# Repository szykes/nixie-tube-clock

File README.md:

# nixie-tube-clock

At first I declared my requirements for my ideal clock. Here are the requirements:
  * No touch working: there shall not be any button or something like that but the clock shall follow daylight saving time or it shall be set after a power outage.
  * Dust resistant: the dust shall not affect the visibility of clock and it shall not be on the PCB and parts.
  * Beautiful: The clock shall have maximum 2 dominant colors (PCB, parts and enclosure).
  
To implement "no touch working" I used a Wifi module to query the accureate time from my home server.
For "dust resistant" requirement I put the clock in a plastic enclosure to procect the core of clock.
"Beautiful" is implemented by selecting white PCB and mostly black parts.

## Docker

```
docker build -t time-server:v1.0 .
docker-compose up -d
```

## Hardware

### Measurements
  * Cathode voltage: 178 V
  * Cathode current: ~800 uA
  * Glim lamp current: ~250 uA
  * Total current: ~220 mA @ 12,2 V without WiFi.
  
### Known issues
  * RBG LED flahes at power-on. The gate of MOSFET of LEDs require a pull-down resistor.
  * PCB design of tube is wrong. The place drawing of tube is mirrored; therefore, digit 7 is digit 4 in real.

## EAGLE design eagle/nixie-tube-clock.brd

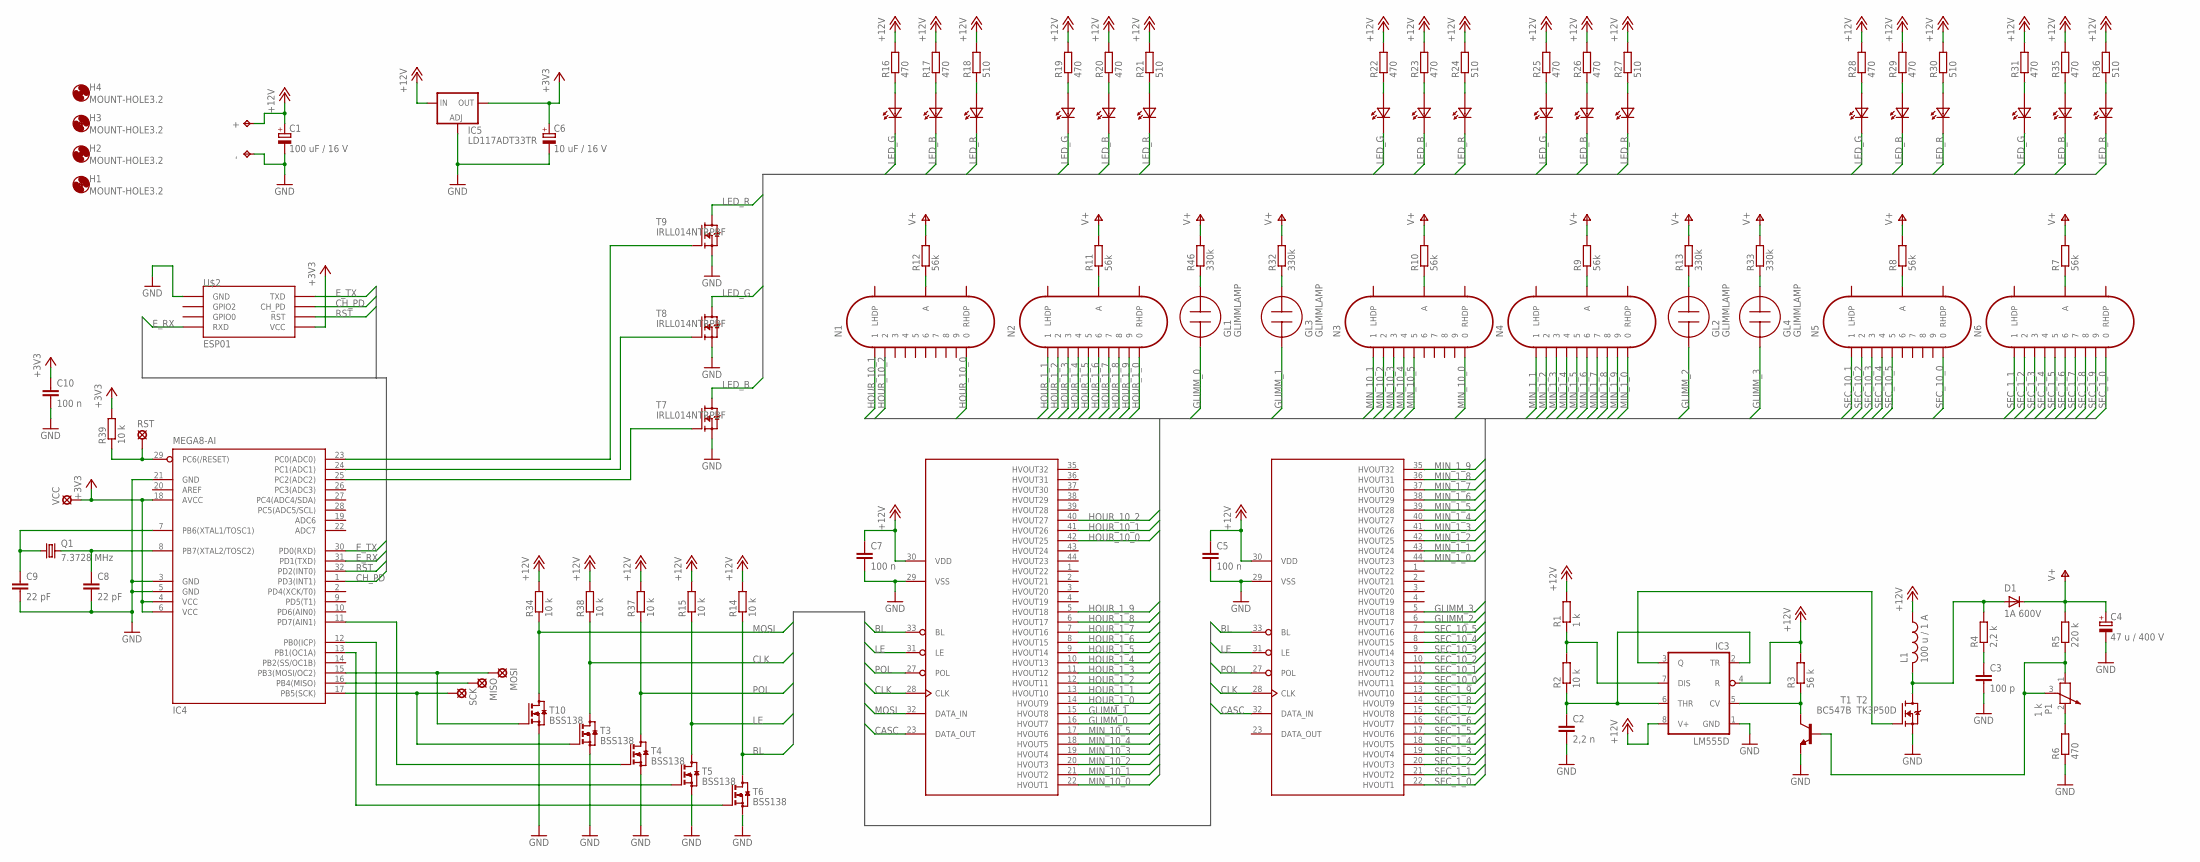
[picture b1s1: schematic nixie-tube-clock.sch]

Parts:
+: +; P1-17
-: -; P1-17
C1: 100 uF / 16 V; 153CLV-0605
C2: 2,2 n; C1206
C3: 100 p; C1206
C4: 47 u / 400 V; E7,5-16
C5, C7, C10: 100 n; C1206
C6: 10 uF / 16 V; 153CLV-0405
C8, C9: 22 pF; C1206
D1: 1A 600V; SMA-DO214AC
GL1, GL2, GL3, GL4: GLIMMLAMP
H1, H2, H3, H4: MOUNT-HOLE3.2; 3,2
IC1, IC2: HV5622QC; PQFP44
IC3: LM555D; SO08
IC4: MEGA8-AI; TQFP32-08
IC5: LD117ADT33TR; DPACK
L1: 100 u / 1 A; L_V_8.7X12_RM5.0
MISO: MISO; SE11
MOSI: MOSI; SE11
N1, N2, N3, N4, N5, N6: IN-14
P1: 1 k; PT-10
Q1: 7.3728 MHz; HC49/S
R1: 1 k; R1206
R2, R14, R15, R34, R37, R38, R39: 10 k; R1206
R3: 56 k; R1206
R4: 2,2 k; R1206
R5: 220 k; R1206
R6, R16, R17, R19, R20, R22, R23, R25, R26, R28, R29, R31, R35: 470; R1206
R7, R8, R9, R10, R11, R12: 56k; R1206
R13, R32, R33, R46: 330k; R1206
R18, R21, R24, R27, R30, R36: 510; R1206
RST: RST; SE11
SCK: SCK; SE11
T1: BC547B; SOT23-BEC
T2: TK3P50D; TO252
T3, T4, T5, T6, T10: BSS138; SOT23
T7, T8, T9: IRLL014NTRPBF; SOT223
U$1, U$3, U$4, U$5, U$6, U$7: OF-SMD5060RGB
U$2: ESP01
VCC: VCC; SE11

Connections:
+3V3: C6.+, C10.1, IC4.4 (VCC), IC4.6 (VCC), IC4.18 (AVCC), IC5.4 (OUT), R39.2, U$2.VCC, VCC.MP
+12V: +.TP, C1.+, C5.1, C7.1, IC1.30 (VDD), IC2.30 (VDD), IC3.4 (R), IC3.8 (V+), IC5.3 (IN), L1.P$1 (1), R1.2, R3.2, R14.2, R15.2, R16.2, R17.2, R18.2, R19.2, R20.2, R21.2, R22.2, R23.2, R24.2, R25.2, R26.2, R27.2, R28.2, R29.2, R30.2, R31.2, R34.2, R35.2, R36.2, R37.2, R38.2
BL: IC1.33 (BL), IC2.33 (BL), R14.1, T6.3 (D)
CASC: IC1.23 (DATA_OUT), IC2.32 (DATA_IN)
CH_PD: IC4.1 (PD3(INT1)), U$2.CH_PD
CLK: IC1.28 (CLK), IC2.28 (CLK), R38.1, T3.3 (D)
E_RX: IC4.31 (PD1(TXD)), U$2.RX (RXD)
E_TX: IC4.30 (PD0(RXD)), U$2.TX (TXD)
GLIMM_0: GL1.C, IC1.16 (HVOUT7)
GLIMM_1: GL3.C, IC1.15 (HVOUT8)
GLIMM_2: GL2.C, IC2.6 (HVOUT17)
GLIMM_3: GL4.C, IC2.5 (HVOUT18)
GND: -.TP, C1.-, C2.2, C3.2, C4.-, C5.2, C6.-, C7.2, C8.2, C9.2, C10.2, IC1.29 (VSS), IC2.29 (VSS), IC3.1 (GND), IC4.3 (GND), IC4.5 (GND), IC4.21 (GND), IC5.1 (ADJ), R6.1, T1.E, T2.2 (S), T3.2 (S), T4.2 (S), T5.2 (S), T6.2 (S), T7.3 (S), T8.3 (S), T9.3 (S), T10.2 (S), U$2.GND
HOUR_1_0: IC1.14 (HVOUT9), N2.0
HOUR_1_1: IC1.13 (HVOUT10), N2.1
HOUR_1_2: IC1.12 (HVOUT11), N2.2
HOUR_1_3: IC1.11 (HVOUT12), N2.3
HOUR_1_4: IC1.10 (HVOUT13), N2.4
HOUR_1_5: IC1.9 (HVOUT14), N2.5
HOUR_1_6: IC1.8 (HVOUT15), N2.6
HOUR_1_7: IC1.7 (HVOUT16), N2.7
HOUR_1_8: IC1.6 (HVOUT17), N2.8
HOUR_1_9: IC1.5 (HVOUT18), N2.9
HOUR_10_0: IC1.42 (HVOUT25), N1.0
HOUR_10_1: IC1.41 (HVOUT26), N1.1
HOUR_10_2: IC1.40 (HVOUT27), N1.2
LE: IC1.31 (LE), IC2.31 (LE), R15.1, T5.3 (D)
LED_B: T7.2 (D), T7.4 (D), U$1.B_CATH (CATH), U$3.B_CATH (CATH), U$4.B_CATH (CATH), U$5.B_CATH (CATH), U$6.B_CATH (CATH), U$7.B_CATH (CATH)
LED_D0: IC4.23 (PC0(ADC0)), T9.1 (G)
LED_D1: IC4.24 (PC1(ADC1)), T8.1 (G)
LED_D2: IC4.25 (PC2(ADC2)), T7.1 (G)
LED_G: T8.2 (D), T8.4 (D), U$1.G_CATH (CATH), U$3.G_CATH (CATH), U$4.G_CATH (CATH), U$5.G_CATH (CATH), U$6.G_CATH (CATH), U$7.G_CATH (CATH)
LED_R: T9.2 (D), T9.4 (D), U$1.R_CATH (CATH), U$3.R_CATH (CATH), U$4.R_CATH (CATH), U$5.R_CATH (CATH), U$6.R_CATH (CATH), U$7.R_CATH (CATH)
MIN_1_0: IC2.44 (HVOUT23), N4.0
MIN_1_1: IC2.43 (HVOUT24), N4.1
MIN_1_2: IC2.42 (HVOUT25), N4.2
MIN_1_3: IC2.41 (HVOUT26), N4.3
MIN_1_4: IC2.40 (HVOUT27), N4.4
MIN_1_5: IC2.39 (HVOUT28), N4.5
MIN_1_6: IC2.38 (HVOUT29), N4.6
MIN_1_7: IC2.37 (HVOUT30), N4.7
MIN_1_8: IC2.36 (HVOUT31), N4.8
MIN_1_9: IC2.35 (HVOUT32), N4.9
MIN_10_0: IC1.22 (HVOUT1), N3.0
MIN_10_1: IC1.21 (HVOUT2), N3.1
MIN_10_2: IC1.20 (HVOUT3), N3.2
MIN_10_3: IC1.19 (HVOUT4), N3.3
MIN_10_4: IC1.18 (HVOUT5), N3.4
MIN_10_5: IC1.17 (HVOUT6), N3.5
MOSI: IC1.32 (DATA_IN), R34.1, T10.3 (D)
unnamed: IC4.29 (PC6(/RESET)), R39.1, RST.MP
unnamed: IC3.7 (DIS), R1.1, R2.2
unnamed: IC3.5 (CV), R3.1, T1.C
unnamed: C2.1, IC3.2 (TR), IC3.6 (THR), R2.1
unnamed: IC3.3 (Q), T2.1 (G)
unnamed: D1.A, L1.P$2 (2), R4.2, T2.3 (D)
unnamed: P1.1, P1.3, R5.1, T1.B
unnamed: C3.1, R4.1
unnamed: P1.2, R6.2
unnamed: N1.A, R12.1
unnamed: N2.A, R11.1
unnamed: N3.A, R10.1
unnamed: N4.A, R9.1
unnamed: N5.A, R8.1
unnamed: N6.A, R7.1
unnamed: IC4.16 (PB4(MISO)), MISO.MP
unnamed: GL2.A, R13.1
unnamed: IC4.13 (PB1(OC1A)), T6.1 (G)
unnamed: R16.1, U$1.G_ANODE (ANODE)
unnamed: R17.1, U$1.B_ANODE (ANODE)
unnamed: R18.1, U$1.R_ANODE (ANODE)
unnamed: C8.1, IC4.8 (PB7(XTAL2/TOSC2)), Q1.2
unnamed: GL3.A, R32.1
unnamed: R19.1, U$3.G_ANODE (ANODE)
unnamed: R20.1, U$3.B_ANODE (ANODE)
unnamed: R21.1, U$3.R_ANODE (ANODE)
unnamed: IC4.12 (PB0(ICP)), T5.1 (G)
unnamed: GL4.A, R33.1
unnamed: C9.1, IC4.7 (PB6(XTAL1/TOSC1)), Q1.1
unnamed: R22.1, U$4.G_ANODE (ANODE)
unnamed: R23.1, U$4.B_ANODE (ANODE)
unnamed: R24.1, U$4.R_ANODE (ANODE)
unnamed: IC4.17 (PB5(SCK)), SCK.MP, T3.1 (G)
unnamed: R25.1, U$5.G_ANODE (ANODE)
unnamed: R26.1, U$5.B_ANODE (ANODE)
unnamed: R27.1, U$5.R_ANODE (ANODE)
unnamed: IC4.15 (PB3(MOSI/OC2)), MOSI.MP, T10.1 (G)
unnamed: IC4.11 (PD7(AIN1)), T4.1 (G)
unnamed: R28.1, U$6.G_ANODE (ANODE)
unnamed: R29.1, U$6.B_ANODE (ANODE)
unnamed: R30.1, U$6.R_ANODE (ANODE)
unnamed: R31.1, U$7.G_ANODE (ANODE)
unnamed: R35.1, U$7.B_ANODE (ANODE)
unnamed: R36.1, U$7.R_ANODE (ANODE)
unnamed: GL1.A, R46.1
POL: IC1.27 (POL), IC2.27 (POL), R37.1, T4.3 (D)
RST: IC4.32 (PD2(INT0)), U$2.RST
SEC_1_0: IC2.22 (HVOUT1), N6.0
SEC_1_1: IC2.21 (HVOUT2), N6.1
SEC_1_2: IC2.20 (HVOUT3), N6.2
SEC_1_3: IC2.19 (HVOUT4), N6.3
SEC_1_4: IC2.18 (HVOUT5), N6.4
SEC_1_5: IC2.17 (HVOUT6), N6.5
SEC_1_6: IC2.16 (HVOUT7), N6.6
SEC_1_7: IC2.15 (HVOUT8), N6.7
SEC_1_8: IC2.14 (HVOUT9), N6.8
SEC_1_9: IC2.13 (HVOUT10), N6.9
SEC_10_0: IC2.12 (HVOUT11), N5.0
SEC_10_1: IC2.11 (HVOUT12), N5.1
SEC_10_2: IC2.10 (HVOUT13), N5.2
SEC_10_3: IC2.9 (HVOUT14), N5.3
SEC_10_4: IC2.8 (HVOUT15), N5.4
SEC_10_5: IC2.7 (HVOUT16), N5.5
V+: C4.+, D1.K (C), R5.2, R7.2, R8.2, R9.2, R10.2, R11.2, R12.2, R13.2, R32.2, R33.2, R46.2

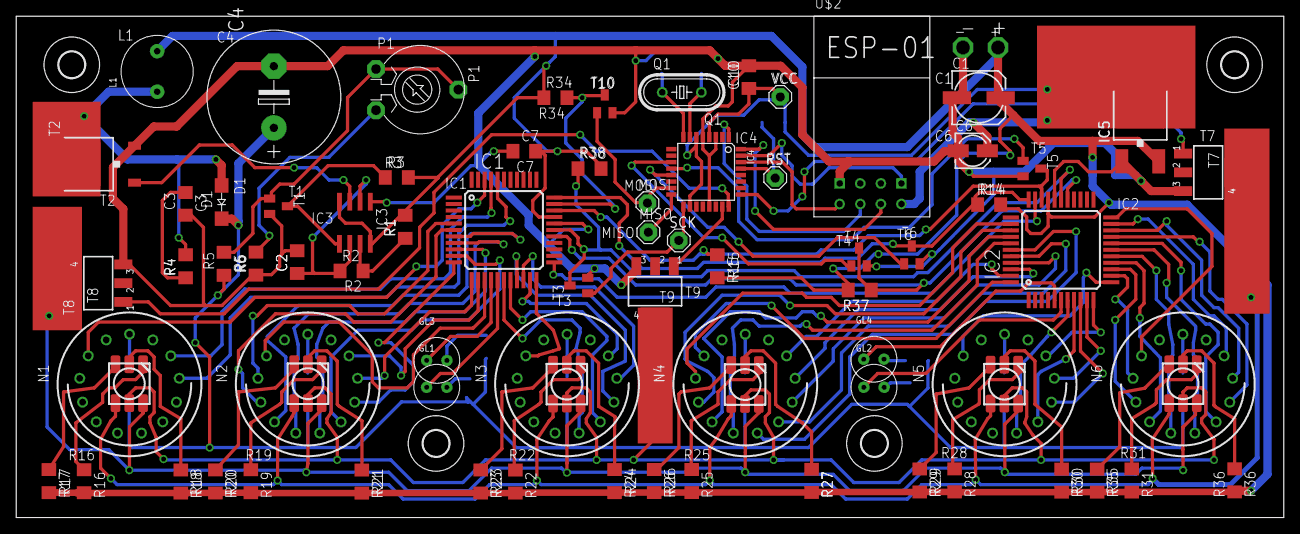
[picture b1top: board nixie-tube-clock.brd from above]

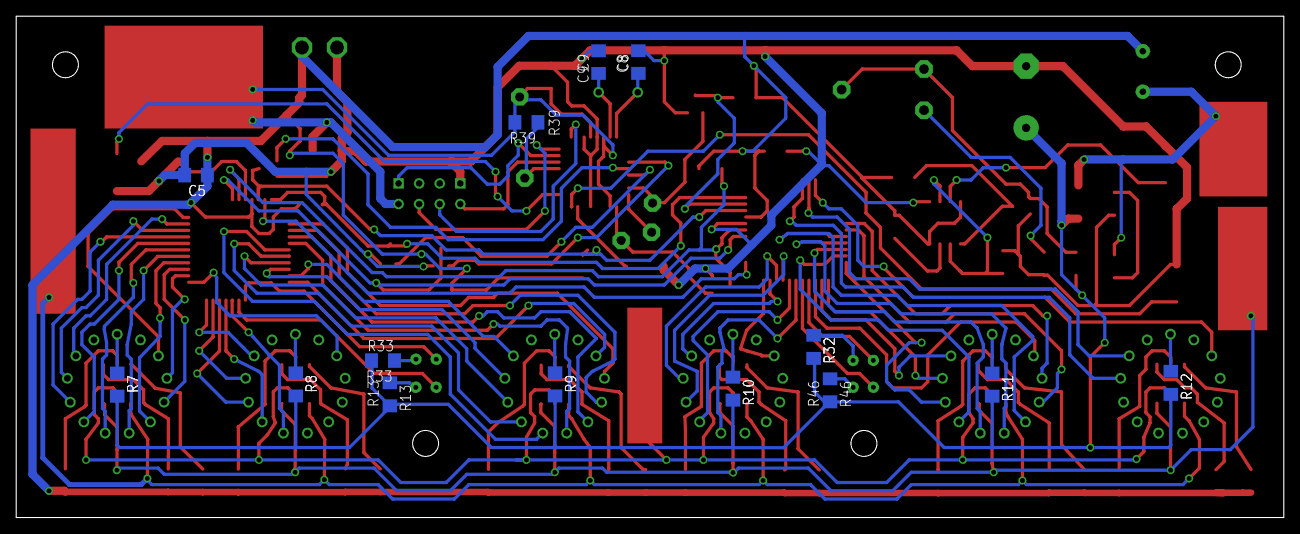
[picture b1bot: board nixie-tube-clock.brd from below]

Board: 2 copper layers, 156.4 x 61.9 mm, 97 parts (14 on the bottom side), 114 nets.

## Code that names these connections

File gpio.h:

#ifndef GPIO_H_
#define GPIO_H_

#include <avr/io.h>

inline void gpio_init(void) {
  DDRB |= (1 << DDB0) | (1 << DDB1) | (1 << DDB3) | (1 << DDB5); // MOSI, SCK
  DDRC |= (1 << DDC0) | (1 << DDC1) | (1 << DDC2);
  DDRD |= (1 << DDD2) | (1 << DDD3) | (1 << DDD7);
}

inline void gpio_led_red_set(void) {
  PORTC |= (1 << PC0);
}

inline void gpio_led_red_reset(void) {
  PORTC &= ~(1 << PC0);
}

inline void gpio_led_green_set(void) {
  PORTC |= (1 << PC1);
}

inline void gpio_led_green_reset(void) {
  PORTC &= ~(1 << PC1);
}

inline void gpio_led_blue_set(void) {
  PORTC |= (1 << PC2);
}

inline void gpio_led_blue_reset(void) {
  PORTC &= ~(1 << PC2);
}

inline void gpio_data_set(void) {
  PORTB |= (1 << PB3);
}

inline void gpio_data_reset(void) {
  PORTB &= ~(1 << PB3);
}

inline void gpio_do_clk_cyc(void) {
  PORTB |= (1 << PB5);
  PORTB &= ~(1 << PB5);
}

inline void gpio_latch_enable_set(void) {
  PORTB |= (1 << PB0);
}

inline void gpio_latch_enable_reset(void) {
  PORTB &= ~(1 << PB0);
}

inline void gpio_blanking_set(void) {
  PORTB |= (1 << PB1);
}

inline void gpio_blanking_reset(void) {
  PORTB &= ~(1 << PB1);
}

inline void gpio_polarity_set(void) {
  PORTD |= (1 << PD7);
}

inline void gpio_polarity_reset(void) {
  PORTD &= ~(1 << PD7);
}

inline void gpio_esp_set(void) {
  PORTD |= (1 << PD2);
}

inline void gpio_esp_reset(void) {
  PORTD &= ~(1 << PD2);
}

inline void gpio_set_ch_pd(void) {
  PORTD |= (1 << PD3);
}

inline void gpio_reset_ch_pd(void) {
  PORTD &= ~(1 << PD3);
}

#endif // GPIO_H_

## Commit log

2022-05-23 Alfa version of schematic
2022-05-24 Alfa v2 version of schematic
2022-05-31 Skeleton for firmware
2022-06-01 Change to 8 MHz
2022-06-01 First version of gpio
2022-06-01 First version of led
2022-06-01 Create wifi package
2022-06-01 First version of clock package
2022-06-01 Alfa version of clock package
2022-06-02 Added watchdog timer
2022-06-02 Small adjustments in led package
2022-06-02 Add dark mode
2022-06-08 Beta version of schematic
2022-06-09 Small update on sch + added PCB
2022-06-17 Add sending and receivin code of UART
2022-06-17 Fixing used F_OSC in the code
2022-06-17 Added at command response timer
2022-06-23 Add server side program
2022-06-23 Added some AT commands + cleanup
2022-06-23 Receiving time data from server works
2022-08-02 Beta version of PCB
2022-08-02 Pre-release version of PCB
2022-08-03 Finalize PCB
2022-08-19 Replaced RGB LED + Gerber files
2022-09-09 Fixing GND issue at IC5 + relocation of C4, P1 and L1
2022-09-18 Some reworks around the HV5622 ans ESP
2022-09-19 Final adjustments
2022-10-30 Make clock working finally
2022-10-30 Sending data via "SPI" but the data itself is not correct yet
2022-10-30 Fix blue led gpio
2022-10-30 Fixing minor issues in CMakeLists.txt
2022-10-30 Clarifying gpio functions
2022-10-30 Move to ATmega8A
2022-10-30 Handling LED ratio correctly + some minor fixes
2022-10-30 Fix the misrouted tubes
2022-11-01 Enable global interrupt at first
2022-11-01 Make ESP01 work
2022-11-01 Add time query func
2022-11-01 Small refactor
2022-11-01 Provide LED ratio info from server
2022-11-01 HV5622 should not be in transparent mode
2022-11-01 Gather LED ratio from server
2022-11-03 Fixed error handling of ESP + regular time querry
2022-11-04 Add some comments
2022-11-04 Align LED ratio slowly
2022-11-08 Fix dark period if statement
2022-11-08 Set wanted blue LED ratio
2022-11-14 Fix dark period -> finally it works as exprected!
2022-11-14 Replace define with const int
2022-11-14 Use RBG LED
2022-11-14 Fix integer overflow
2022-11-14 Fix reset pins of RBG LED
2022-11-14 Zero ratios of RGB LED
2022-11-14 Remove RGB colors
2022-11-16 Add docker support
2022-12-11 Fix time handling at 23:59:59
2024-04-09 updated Dockerfile + server binary
2024-04-09 add gh workflow verify for server side
2024-04-09 add bulding and pushing docker image GH workflow
2024-04-09 add GH workflow for verifying clock source
2024-04-10 move gpio funcs
2024-04-10 rework main file
2024-04-10 rework wifi
2024-04-10 rework led
2024-04-10 remove unused include
2024-05-11 add test framework
2024-05-11 cover wifi.c with test
2024-05-16 refactor mock fw
2024-05-23 cover led.c with tests
2024-06-05 cover clock.c with tests
2024-06-07 query time at noon only
2024-06-07 refactor clock testing
2024-06-08 fix counter handling in interrupt handler of clock.c
2024-06-08 remove led dark period function call from clock.c
2024-06-08 fix type of iterators
2024-06-08 removed dark period flag in led.c
2024-06-08 rework TC handling
2024-06-08 make led common for tests
2024-06-08 change RGB values
2024-06-08 format the code
2024-06-08 fix warnings
2024-06-08 change modifier again
2024-06-08 add tests to GH workflow
2024-06-10 fix rgb led ratio issue
2024-06-10 fix wifi query issue at init
2024-06-10 fix rgb issue
2024-06-10 query time via wifi times rework
2024-06-10 change init time
2024-06-11 Refactor everything (#1)
    * updated Dockerfile + server binary
    * add gh workflow verify for server side
    * add bulding and pushing docker image GH workflow
    * add GH workflow for verifying clock source
    * move gpio funcs
    * rework main file
2024-06-11 Revert "Refactor everything (#1)"
    This reverts commit e1160aecb3f4056ec246d98de306e112ccf4a9c1.
2026-02-26 feat: use go 1.26.0 and use scratch image
2026-02-26 fix: make more resilient main.go
2026-02-26 fix: errcheck findings
